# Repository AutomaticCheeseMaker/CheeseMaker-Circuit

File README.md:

# CheeseMaker-Circuit

This is the circuit board for the hardware that controls the stirring machine. On top of this circuit you'll need:

- A stepper driver, e.g. A4988
- 1-2 DS18B20 Temperature Sensors
- SSR for switching on Water Heater (Kettle Element)
- Arduino Mega 2560
- 3x 4.7 kohm resistors
- LM2596 DC to DC Buck Converter (Convert input voltage to 5V)
- Connectors (or plain pin headers) - I used JST-XH socket for the stepper output, KF2510 for the temp sensor input

Notes:

- The schematics assume 24V input. This is because my stepper was 24V. Note that Arduino Mega 2560 isn't 24V tolerant which is why the LM2596 is required.

## CheeseDistribution
To reduce the jitter on the servos this second circuit was developed to sit on the stirrer arm servo and distribute all the connections out to the stepper and servo.

The connection between this board and the main one is via a 20 pin IDC cable.

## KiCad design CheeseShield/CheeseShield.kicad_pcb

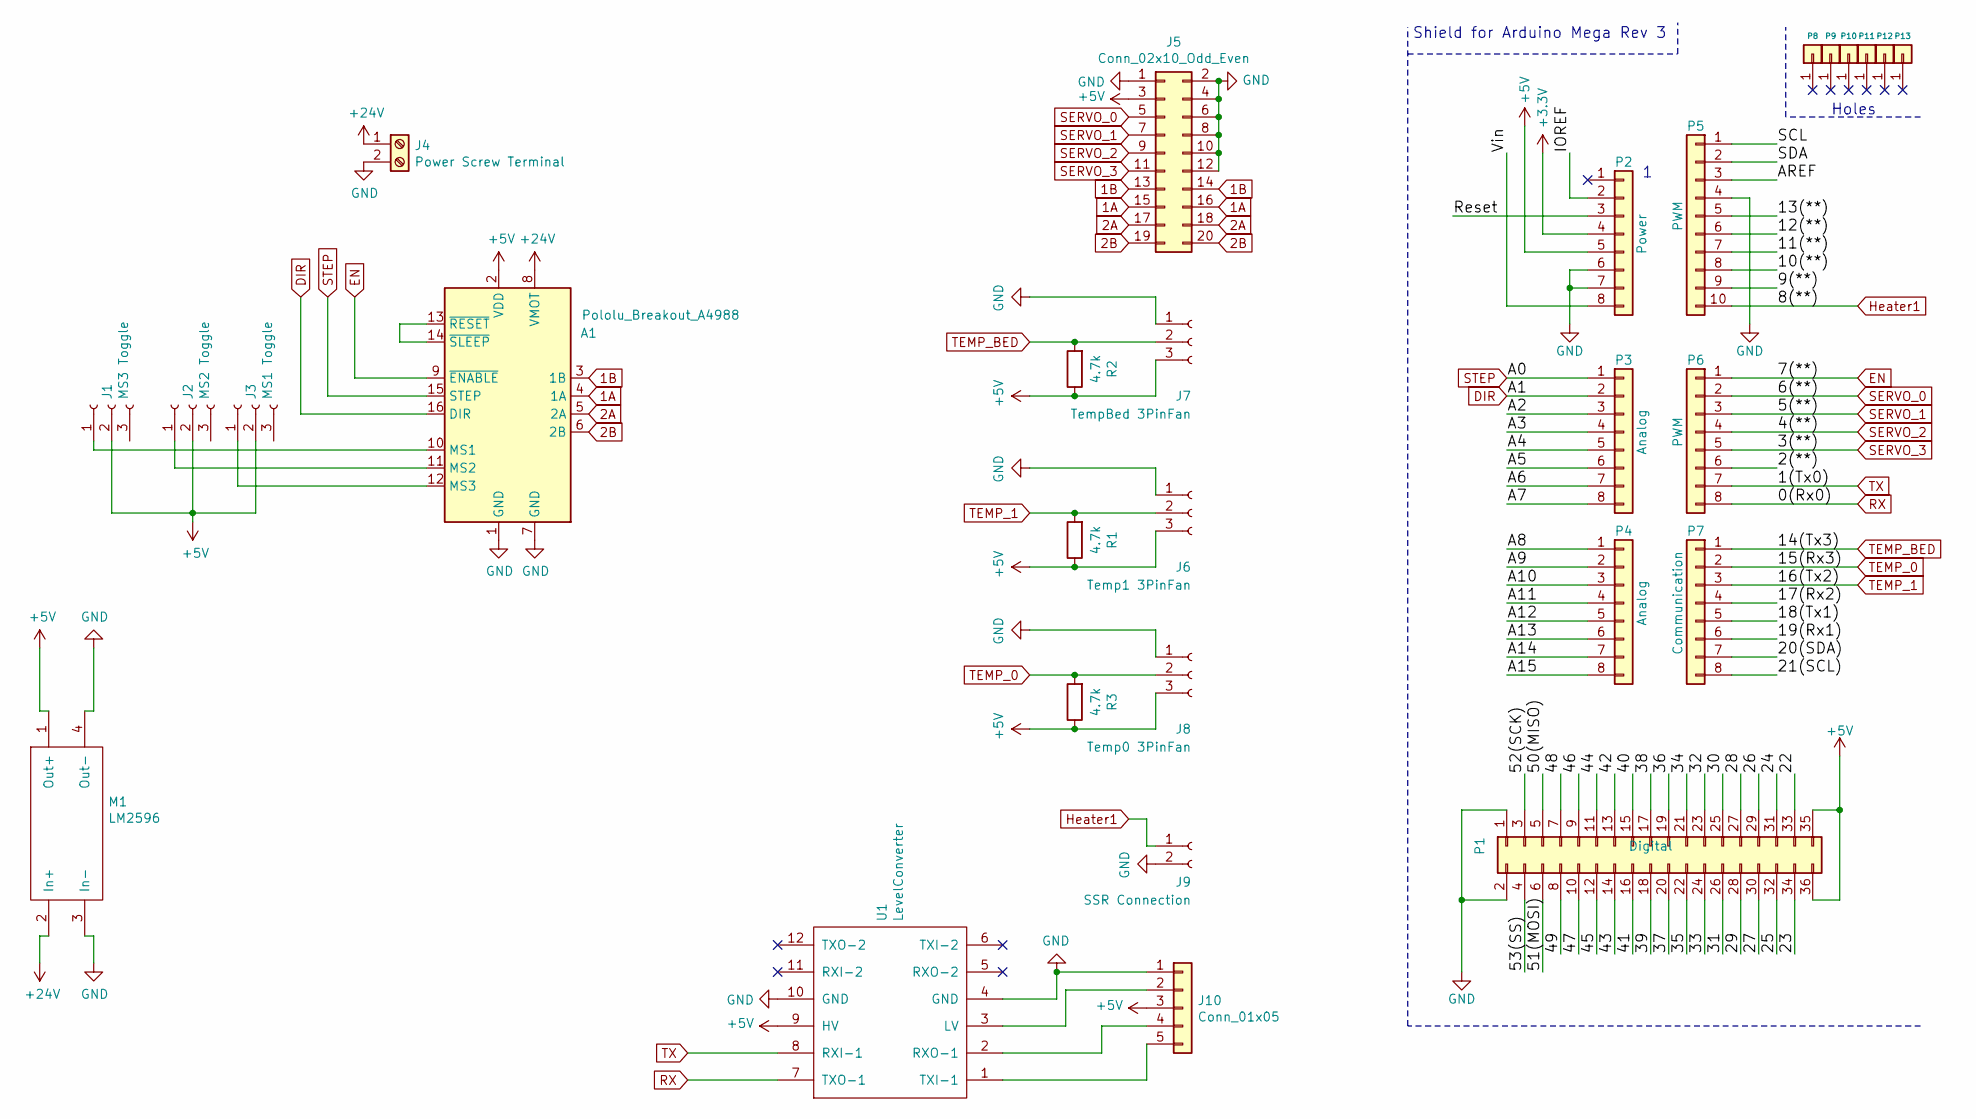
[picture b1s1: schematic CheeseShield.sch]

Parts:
A1: Pololu_Breakout_A4988; Pololu_Breakout-16_15.2x20.3mm
J1: MS3 Toggle; Pin_Header_Straight_1x03_Pitch2.54mm
J2: MS2 Toggle; Pin_Header_Straight_1x03_Pitch2.54mm
J3: MS1 Toggle; Pin_Header_Straight_1x03_Pitch2.54mm
J4: Power Screw Terminal; TerminalBlock_bornier-2_P5.08mm
J5: Conn_02x10_Odd_Even; IDC-Header_2x10_P2.54mm_Vertical
J6: Temp1 3PinFan; Fan_Pin_Header_Straight_1x03
J7: TempBed 3PinFan; Fan_Pin_Header_Straight_1x03
J8: Temp0 3PinFan; Fan_Pin_Header_Straight_1x03
J9: SSR Connection; JST_XH_B02B-XH-A_02x2.50mm_Straight
J10: Conn_01x05; PinHeader_1x05_P2.54mm_Vertical
M1: LM2596
P1: Digital; Socket_Strip_Arduino_2x18
P2: Power; Socket_Strip_Arduino_1x08
P3, P4: Analog; Socket_Strip_Arduino_1x08
P5: PWM; Socket_Strip_Arduino_1x10
P6: PWM; Socket_Strip_Arduino_1x08
P7: Communication; Socket_Strip_Arduino_1x08
P8, P9, P10, P11, P12, P13: CONN_01X01; Arduino_1pin
R1, R2, R3: 4.7k; R_Axial_DIN0207_L6.3mm_D2.5mm_P7.62mm_Horizontal
U1: LevelConverter

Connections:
1A: A1.4 (1A), J5.15, J5.16
1B: A1.3 (1B), J5.13, J5.14
2A: A1.5 (2A), J5.17, J5.18
2B: A1.6 (2B), J5.19, J5.20
+3V3: P2.4
+5V: A1.2 (VDD), J1.2, J2.2, J3.2, J5.3, J6.3, J7.3, J8.3, J10.3, M1.1 (Out+), P1.35, P1.36, P2.5, R1.1, R2.1, R3.1, U1.9 (HV)
+24V: A1.8 (VMOT), J4.1, M1.2 (In+)
/2(**): P6.6
/9(**): P5.9
/10(**): P5.8
/11(**): P5.7
/12(**): P5.6
/13(**): P5.5
/17(Rx2): P7.4
/18(Tx1): P7.5
/19(Rx1): P7.6
/20(SDA): P7.7
/21(SCL): P7.8
/22: P1.33
/23: P1.34
/24: P1.31
/25: P1.32
/26: P1.29
/27: P1.30
/28: P1.27
/29: P1.28
/30: P1.25
/31: P1.26
/32: P1.23
/33: P1.24
/34: P1.21
/35: P1.22
/36: P1.19
/37: P1.20
/38: P1.17
/39: P1.18
/40: P1.15
/41: P1.16
/42: P1.13
/43: P1.14
/44: P1.11
/45: P1.12
/46: P1.9
/47: P1.10
/48: P1.7
/49: P1.8
/50(MISO): P1.5
/51(MOSI): P1.6
/52(SCK): P1.3
/53(SS): P1.4
/A2: P3.3
/A3: P3.4
/A4: P3.5
/A5: P3.6
/A6: P3.7
/A7: P3.8
/A8: P4.1
/A9: P4.2
/A10: P4.3
/A11: P4.4
/A12: P4.5
/A13: P4.6
/A14: P4.7
/A15: P4.8
/AREF: P5.3
/IOREF: P2.2
/Reset: P2.3
/SCL: P5.1
/SDA: P5.2
/Vin: P2.8
DIR: A1.16 (DIR), P3.2
EN: A1.9 (~ENABLE), P6.1
GND: A1.1 (GND), A1.7 (GND), J4.2, J5.1, J5.2, J5.4, J5.6, J5.8, J5.10, J5.12, J6.1, J7.1, J8.1, J9.2, J10.1, M1.3 (In-), M1.4 (Out-), P1.1, P1.2, P2.6, P2.7, P5.4, U1.4 (GND), U1.10 (GND)
Heater1: J9.1, P5.10
unnamed: A1.10 (MS1), J1.1
unnamed: A1.11 (MS2), J2.1
unnamed: A1.12 (MS3), J3.1
unnamed: A1.13 (~RESET), A1.14 (~SLEEP)
unnamed: J10.2, U1.3 (LV)
unnamed: J10.4, U1.2 (RXO-1)
unnamed: J10.5, U1.1 (TXI-1)
RX: P6.8, U1.7 (TXO-1)
SERVO_0: J5.5, P6.2
SERVO_1: J5.7, P6.3
SERVO_2: J5.9, P6.4
SERVO_3: J5.11, P6.5
STEP: A1.15 (STEP), P3.1
TEMP_0: J8.2, P7.2, R3.2
TEMP_1: J6.2, P7.3, R1.2
TEMP_BED: J7.2, P7.1, R2.2
TX: P6.7, U1.8 (RXI-1)

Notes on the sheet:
Shield for Arduino Mega Rev 3
Holes

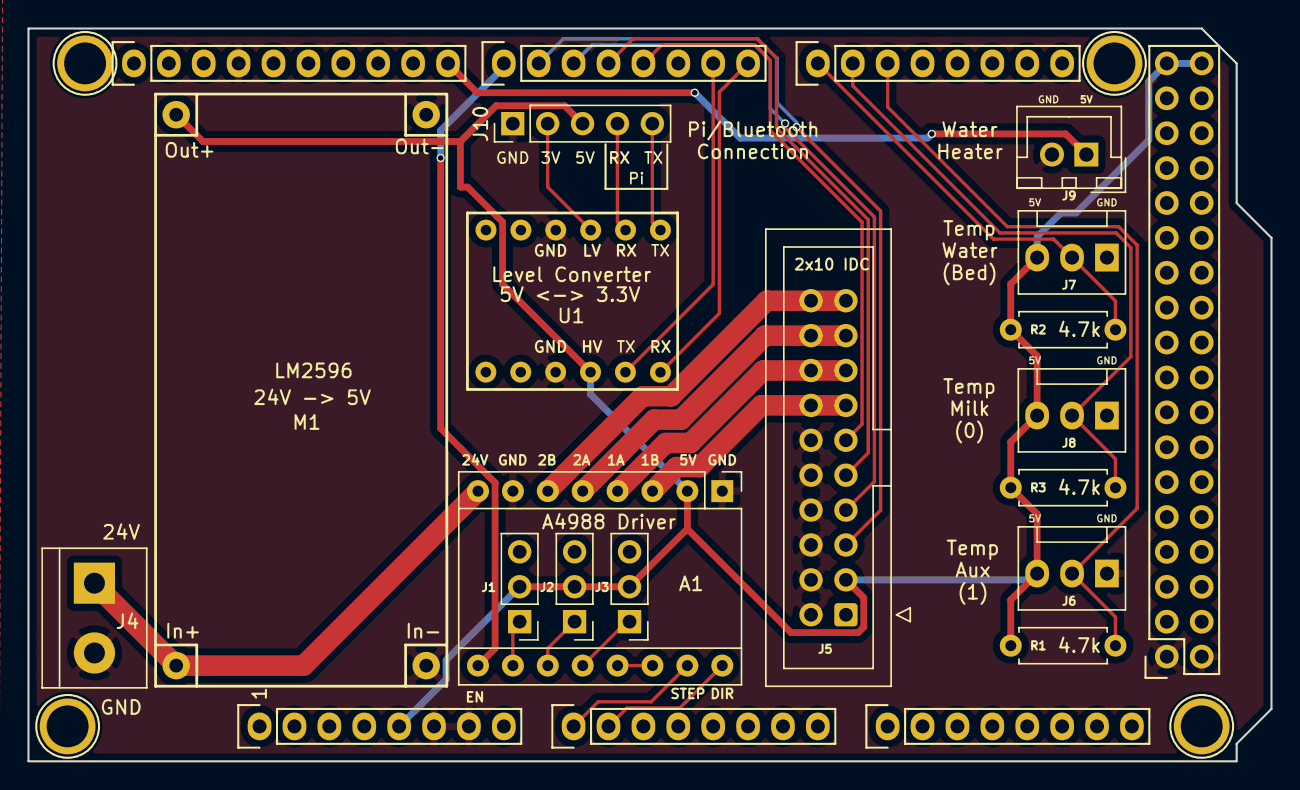
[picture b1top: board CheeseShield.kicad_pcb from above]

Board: 2 copper layers, 90.5 x 53.3 mm, 27 parts (0 on the bottom side), 27 nets.

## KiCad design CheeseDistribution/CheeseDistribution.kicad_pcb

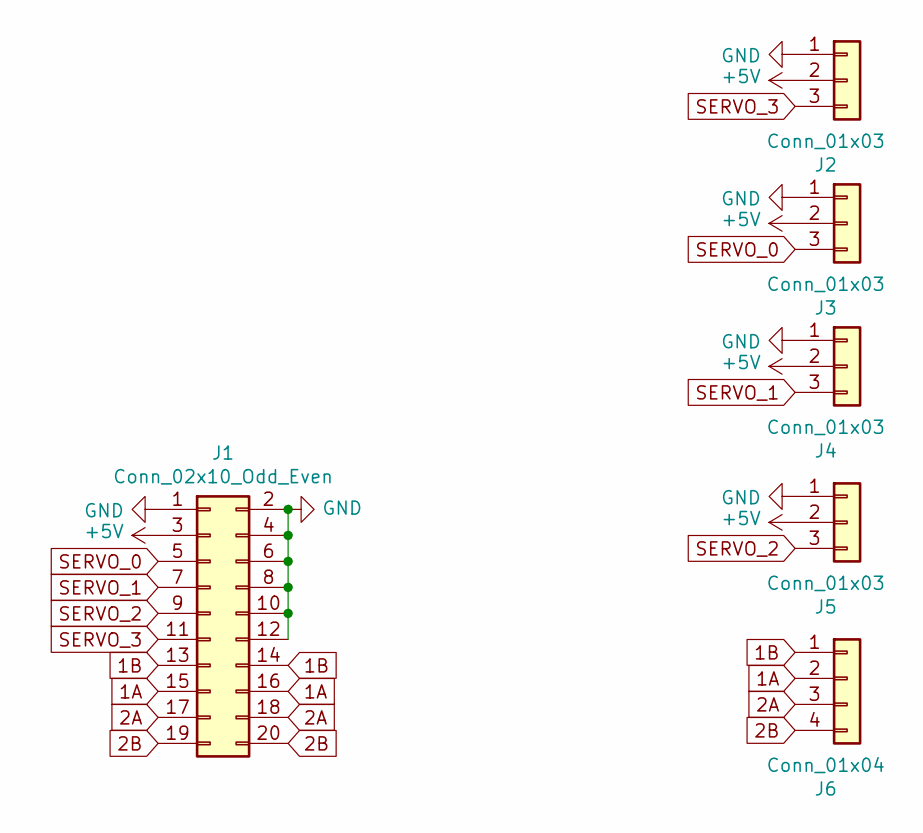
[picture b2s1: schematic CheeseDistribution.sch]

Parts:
J1: Conn_02x10_Odd_Even; IDC-Header_2x10_P2.54mm_Vertical
J2, J3, J4, J5: Conn_01x03; PinHeader_1x03_P2.54mm_Horizontal
J6: Conn_01x04; JST_XH_B4B-XH-A_1x04_P2.50mm_Vertical

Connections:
1A: J1.15, J1.16, J6.2
1B: J1.13, J1.14, J6.1
2A: J1.17, J1.18, J6.3
2B: J1.19, J1.20, J6.4
+5V: J1.3, J2.2, J3.2, J4.2, J5.2
GND: J1.1, J1.2, J1.4, J1.6, J1.8, J1.10, J1.12, J2.1, J3.1, J4.1, J5.1
SERVO_0: J1.5, J3.3
SERVO_1: J1.7, J4.3
SERVO_2: J1.9, J5.3
SERVO_3: J1.11, J2.3

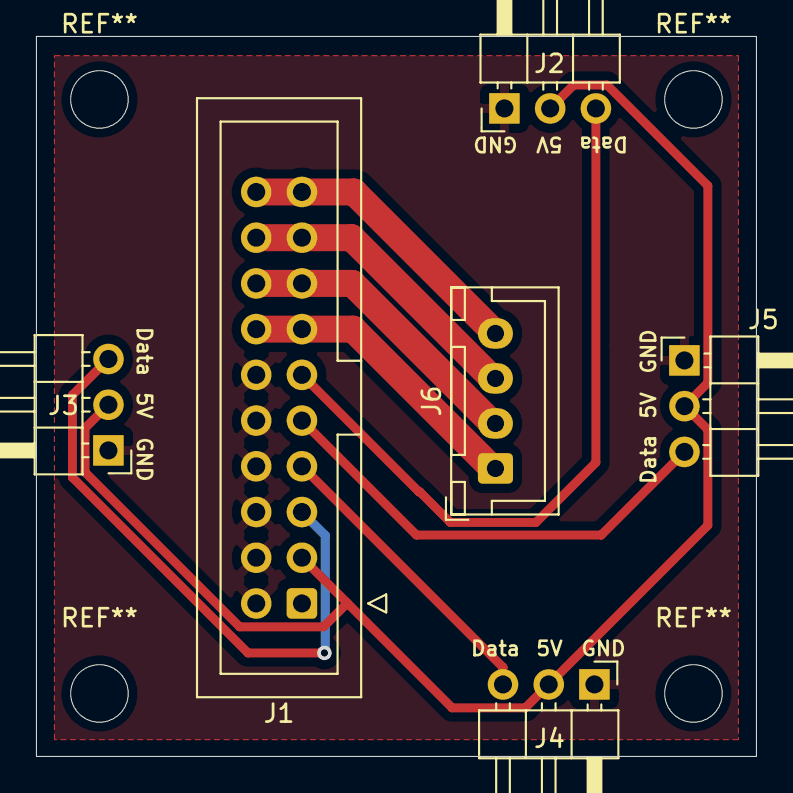
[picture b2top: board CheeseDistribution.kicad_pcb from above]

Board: 2 copper layers, 40.0 x 40.0 mm, 6 parts (0 on the bottom side), 10 nets.

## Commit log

2019-12-09 Initial commit of board schematic
2019-12-09 Added in parts library
2020-01-31 feat: Added in bluetooth and servo headers
2021-08-15 feat: updated circuit to minimize servo jitter
2021-08-15 feat: add in images
